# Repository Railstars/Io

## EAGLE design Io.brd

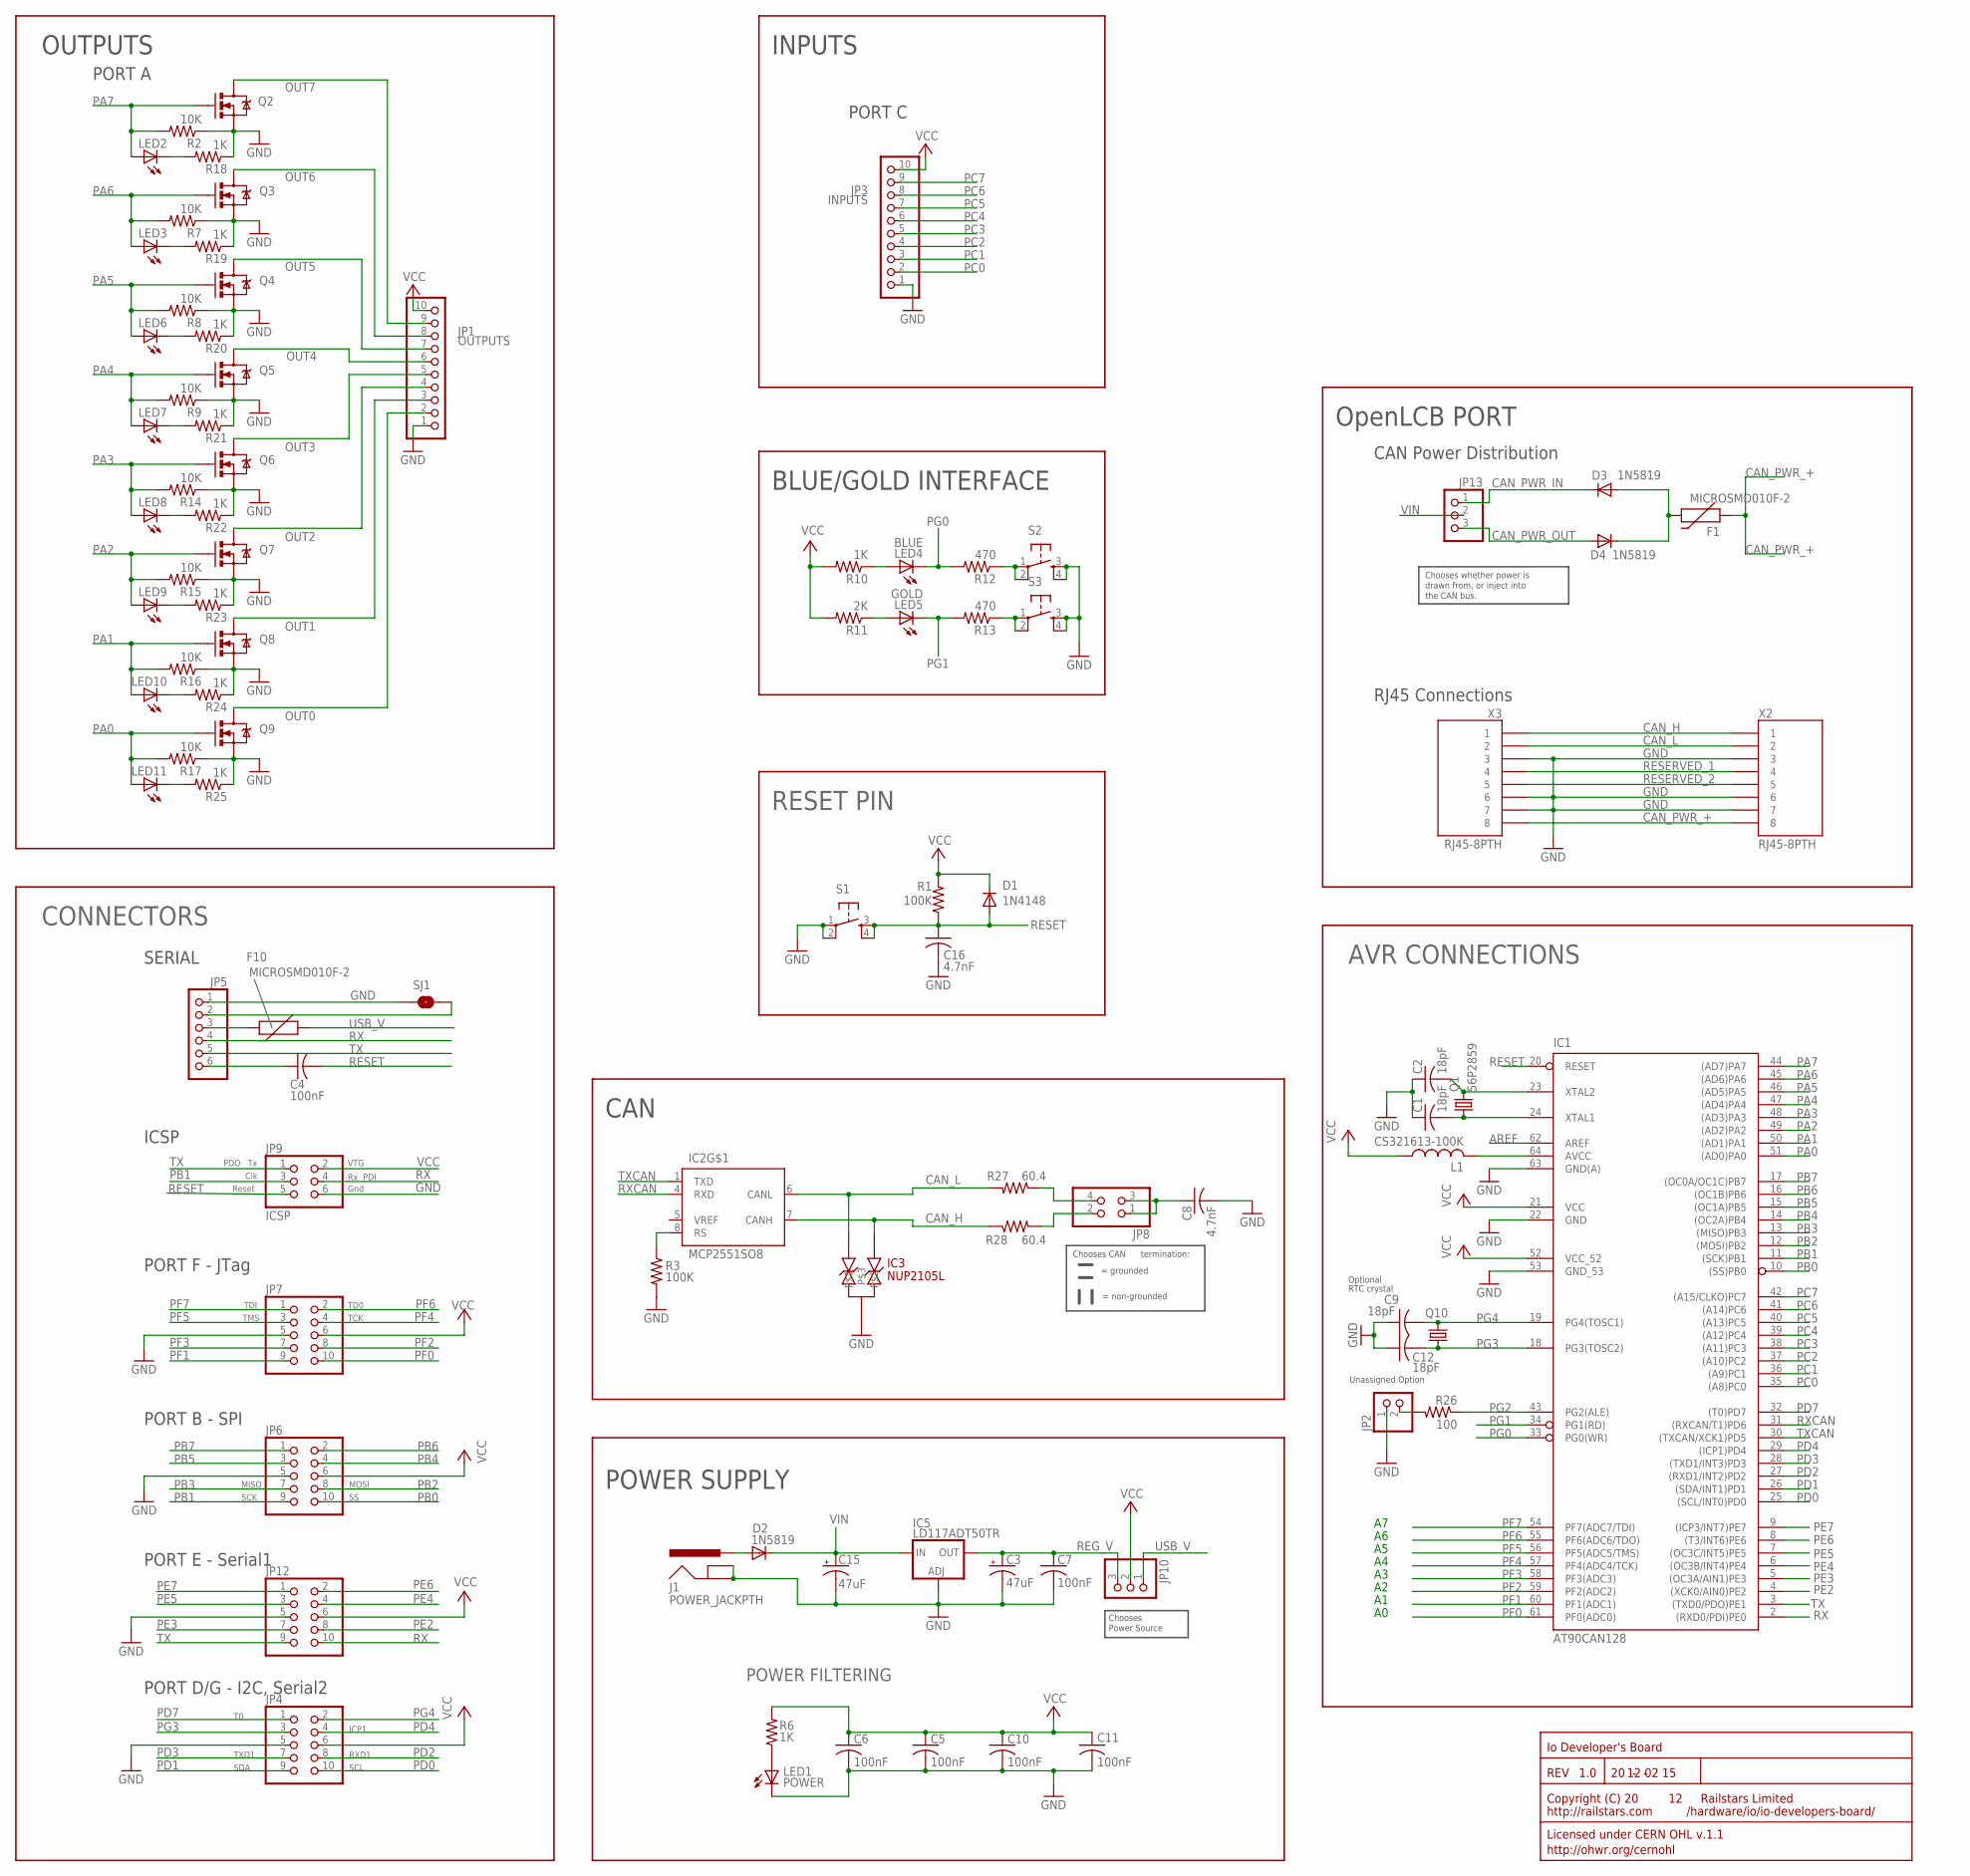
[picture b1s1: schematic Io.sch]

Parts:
C1, C2, C9, C12: 18pF; C0805
C3, C15: 47uF; UD-6,3X5,8_NICHICON
C4, C5, C6, C7, C10, C11: 100nF; C0805
C8, C16: 4.7nF; C0805
D1: 1N4148; SOD123
D2, D3, D4: 1N5819; SMA-DIODE
F1, F10: MICROSMD010F-2; PTC-1206
IC1: AT90CAN128; TQFP64
IC2: MCP2551SO8; SO08
IC3: NUP2105L; SOT-23
IC5: LD117ADT50TR; DPACK
J1: POWER_JACKPTH; POWER_JACK_PTH
JP1: OUTPUTS; 1X10
JP2: PINHD-1X2; 1X02
JP3: INPUTS; 1X10
JP4, JP6, JP7, JP12: 2X5_HEADERSHROUDED; 2X5_SHROUD
JP5: PINHD-1X6; 1X06
JP8: PINHD-2X2; 2X02
JP9: ICSP; 2X03
JP10, JP13: PINHD-1X3; 1X03
L1: CS321613-100K; L3216C
LED1: POWER; CHIP-LED0805
LED2, LED3, LED6, LED7, LED8, LED9, LED10, LED11: LEDCHIP-LED0805; CHIP-LED0805
LED4: BLUE; CHIP-LED0805
LED5: GOLD; CHIP-LED0805
Q1: 56P2859; HC49/S
Q2, Q3, Q4, Q5, Q6, Q7, Q8, Q9: PMV56XN; SOT23-3
Q10: CRYSTALTC26V; TC26V
R1, R3: 100K; R0805
R2, R7, R8, R9, R14, R15, R16, R17: 10K; R0805
R6, R10, R18, R19, R20, R21, R22, R23, R24, R25: 1K; R0805
R11: 2K; R0805
R12, R13: 470; R0805
R26: 100; R0805
R27, R28: 60.4; R1206
S1, S2, S3: TAC_SWITCHPTH; TACTILE-PTH
SJ1: SOLDERJUMPERTRACE; SJ_2S-TRACE
U$4: RAILSTARS_LOGO50MM; RAILSTARS_50MM
X2, X3: RJ45-8PTH; RJ45-8

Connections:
AREF: IC1.62 (AREF)
CAN_H: IC2.7 (CANH), IC3.2, R28.1, X2.1, X3.1
CAN_L: IC2.6 (CANL), IC3.1, R27.2, X2.2, X3.2
CAN_PWR_+: F1.1, X2.8, X3.8
CAN_PWR_IN: D3.C, JP13.1
CAN_PWR_OUT: D4.A, JP13.3
GND: C1.1, C2.1, C3.-, C5.2, C6.2, C7.2, C8.2, C9.1, C10.2, C11.2, C12.1, C15.-, C16.2, IC1.22 (GND), IC1.53 (GND_53), IC1.63 (GND(A)), IC2.2 (GND), IC3.3, IC5.1 (ADJ), J1.GND, J1.GNDBREAK, JP1.1, JP2.1, JP3.1, JP4.5, JP5.1, JP6.5, JP7.5, JP9.6, JP12.5, LED1.C, Q2.2 (S), Q3.2 (S), Q4.2 (S), Q5.2 (S), Q6.2 (S), Q7.2 (S), Q8.2 (S), Q9.2 (S), R2.1, R3.2, R7.1, R8.1, R9.1, R14.1, R15.1, R16.1, R17.1, R18.1, R19.1, R20.1, R21.1, R22.1, R23.1, R24.1, R25.1, S1.1, S1.2, S2.3, S2.4, S3.3, S3.4, SJ1.2, X2.3, X2.6, X2.7, X3.3, X3.6, X3.7
unnamed: JP8.2, R28.2
unnamed: JP8.4, R27.1
unnamed: LED4.A, R10.1
unnamed: LED5.A, R11.1
unnamed: IC2.8 (RS), R3.1
unnamed: R12.1, S2.1, S2.2
unnamed: F10.2, JP5.3
unnamed: LED1.A, R6.1
unnamed: D2.A, J1.PWR
unnamed: C1.2, IC1.24 (XTAL1), Q1.1
unnamed: R13.1, S3.1, S3.2
unnamed: LED10.C, R24.2
unnamed: LED9.C, R23.2
unnamed: LED8.C, R22.2
unnamed: D3.A, D4.C, F1.2
unnamed: LED7.C, R21.2
unnamed: LED6.C, R20.2
unnamed: LED3.C, R19.2
unnamed: LED2.C, R18.2
unnamed: LED11.C, R25.2
unnamed: IC1.64 (AVCC), L1.2
unnamed: JP5.2, SJ1.1
unnamed: C8.1, JP8.1, JP8.3
unnamed: JP2.2, R26.2
unnamed: C4.1, JP5.6
OUT0: JP1.2, Q9.3 (D)
OUT1: JP1.3, Q8.3 (D)
OUT2: JP1.4, Q7.3 (D)
OUT3: JP1.5, Q6.3 (D)
OUT4: JP1.6, Q5.3 (D)
OUT5: JP1.7, Q4.3 (D)
OUT6: JP1.8, Q3.3 (D)
OUT7: JP1.9, Q2.3 (D)
PA0: IC1.51 ((AD0)PA0), LED11.A, Q9.1 (G), R17.2
PA1: IC1.50 ((AD1)PA1), LED10.A, Q8.1 (G), R16.2
PA2: IC1.49 ((AD2)PA2), LED9.A, Q7.1 (G), R15.2
PA3: IC1.48 ((AD3)PA3), LED8.A, Q6.1 (G), R14.2
PA4: IC1.47 ((AD4)PA4), LED7.A, Q5.1 (G), R9.2
PA5: IC1.46 ((AD5)PA5), LED6.A, Q4.1 (G), R8.2
PA6: IC1.45 ((AD6)PA6), LED3.A, Q3.1 (G), R7.2
PA7: IC1.44 ((AD7)PA7), LED2.A, Q2.1 (G), R2.2
PB0: IC1.10 ((SS)PB0), JP6.10
PB1: IC1.11 ((SCK)PB1), JP6.9, JP9.3
PB2: IC1.12 ((MOSI)PB2), JP6.8
PB3: IC1.13 ((MISO)PB3), JP6.7
PB4: IC1.14 ((OC2A)PB4), JP6.4
PB5: IC1.15 ((OC1A)PB5), JP6.3
PB6: IC1.16 ((OC1B)PB6), JP6.2
PB7: IC1.17 ((OC0A/OC1C)PB7), JP6.1
PC0: IC1.35 ((A8)PC0), JP3.2
PC1: IC1.36 ((A9)PC1), JP3.3
PC2: IC1.37 ((A10)PC2), JP3.4
PC3: IC1.38 ((A11)PC3), JP3.5
PC4: IC1.39 ((A12)PC4), JP3.6
PC5: IC1.40 ((A13)PC5), JP3.7
PC6: IC1.41 ((A14)PC6), JP3.8
PC7: IC1.42 ((A15/CLKO)PC7), JP3.9
PD0: IC1.25 ((SCL/INT0)PD0), JP4.10
PD1: IC1.26 ((SDA/INT1)PD1), JP4.9
PD2: IC1.27 ((RXD1/INT2)PD2), JP4.8
PD3: IC1.28 ((TXD1/INT3)PD3), JP4.7
PD4: IC1.29 ((ICP1)PD4), JP4.4
PD7: IC1.32 ((T0)PD7), JP4.1
PE2: IC1.4 ((XCK0/AIN0)PE2), JP12.8
PE3: IC1.5 ((OC3A/AIN1)PE3), JP12.7
PE4: IC1.6 ((OC3B/INT4)PE4), JP12.4
PE5: IC1.7 ((OC3C/INT5)PE5), JP12.3
PE6: IC1.8 ((T3/INT6)PE6), JP12.2
PE7: IC1.9 ((ICP3/INT7)PE7), JP12.1
PF0: IC1.61 (PF0(ADC0)), JP7.10
PF1: IC1.60 (PF1(ADC1)), JP7.9
PF2: IC1.59 (PF2(ADC2)), JP7.8
PF3: IC1.58 (PF3(ADC3)), JP7.7
PF4: IC1.57 (PF4(ADC4/TCK)), JP7.4
PF5: IC1.56 (PF5(ADC5/TMS)), JP7.3
PF6: IC1.55 (PF6(ADC6/TDO)), JP7.2
PF7: IC1.54 (PF7(ADC7/TDI)), JP7.1
PG0: IC1.33 (PG0(WR)), LED4.C, R12.2
PG1: IC1.34 (PG1(RD)), LED5.C, R13.2
PG2: IC1.43 (PG2(ALE)), R26.1
PG3: C12.2, IC1.18 (PG3(TOSC2)), JP4.3, Q10.1
PG4: C9.2, IC1.19 (PG4(TOSC1)), JP4.2, Q10.2
REG_V: C3.+, C7.1, IC5.4 (OUT), JP10.3
RESERVED_1: X2.4, X3.4
RESERVED_2: X2.5, X3.5
RESET: C4.2, C16.1, D1.A, IC1.20 (RESET), JP9.5, R1.1, S1.3, S1.4
RX: IC1.2 ((RXD0/PDI)PE0), JP5.4, JP9.4, JP12.10
RXCAN: IC1.31 ((RXCAN/T1)PD6), IC2.4 (RXD)
TX: IC1.3 ((TXD0/PDO)PE1), JP5.5, JP9.1, JP12.9
TXCAN: IC1.30 ((TXCAN/XCK1)PD5), IC2.1 (TXD)
USB_V: F10.1, JP10.1
VCC: C5.1, C6.1, C10.1, C11.1, D1.C, IC1.21 (VCC), IC1.52 (VCC_52), IC2.3 (VCC), JP1.10, JP3.10, JP4.6, JP6.6, JP7.6, JP9.2, JP10.2, JP12.6, L1.1, R1.2, R6.2, R10.2, R11.2
VIN: C15.+, D2.C, IC5.3 (IN), JP13.2
XTAL1: C2.2, IC1.23 (XTAL2), Q1.2

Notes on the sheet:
POWER SUPPLY
OpenLCB PORT
CAN
POWER FILTERING
RESET PIN
AVR CONNECTIONS
Io Developer's Board
12 02 15
1.0
/hardware/io/io-developers-board/
BLUE/GOLD INTERFACE
Licensed under CERN OHL v.1.1
http://ohwr.org/cernohl
VTG
Clk
Gnd
Reset
TDI
TD0
TMS
TCK
SCL
SDA
RXD1
TXD1
ICP1
SCK
MOSI
MISO
PDO
PDI
INPUTS
OUTPUTS
CONNECTORS
PORT F - JTag
PORT B - SPI
PORT E - Serial1
PORT D/G - I2C, Serial2
PORT A
PORT C

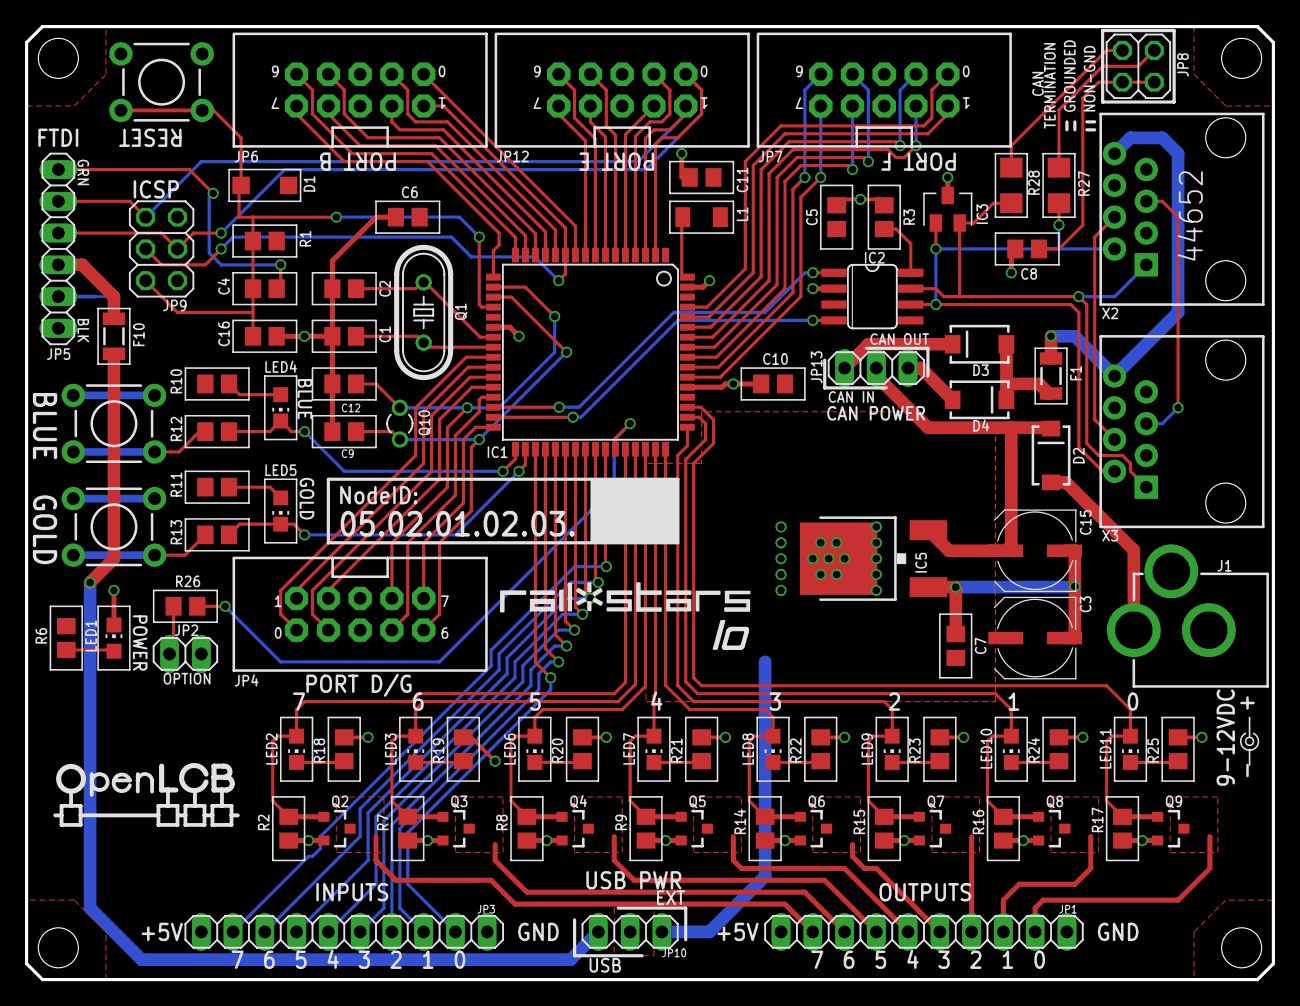
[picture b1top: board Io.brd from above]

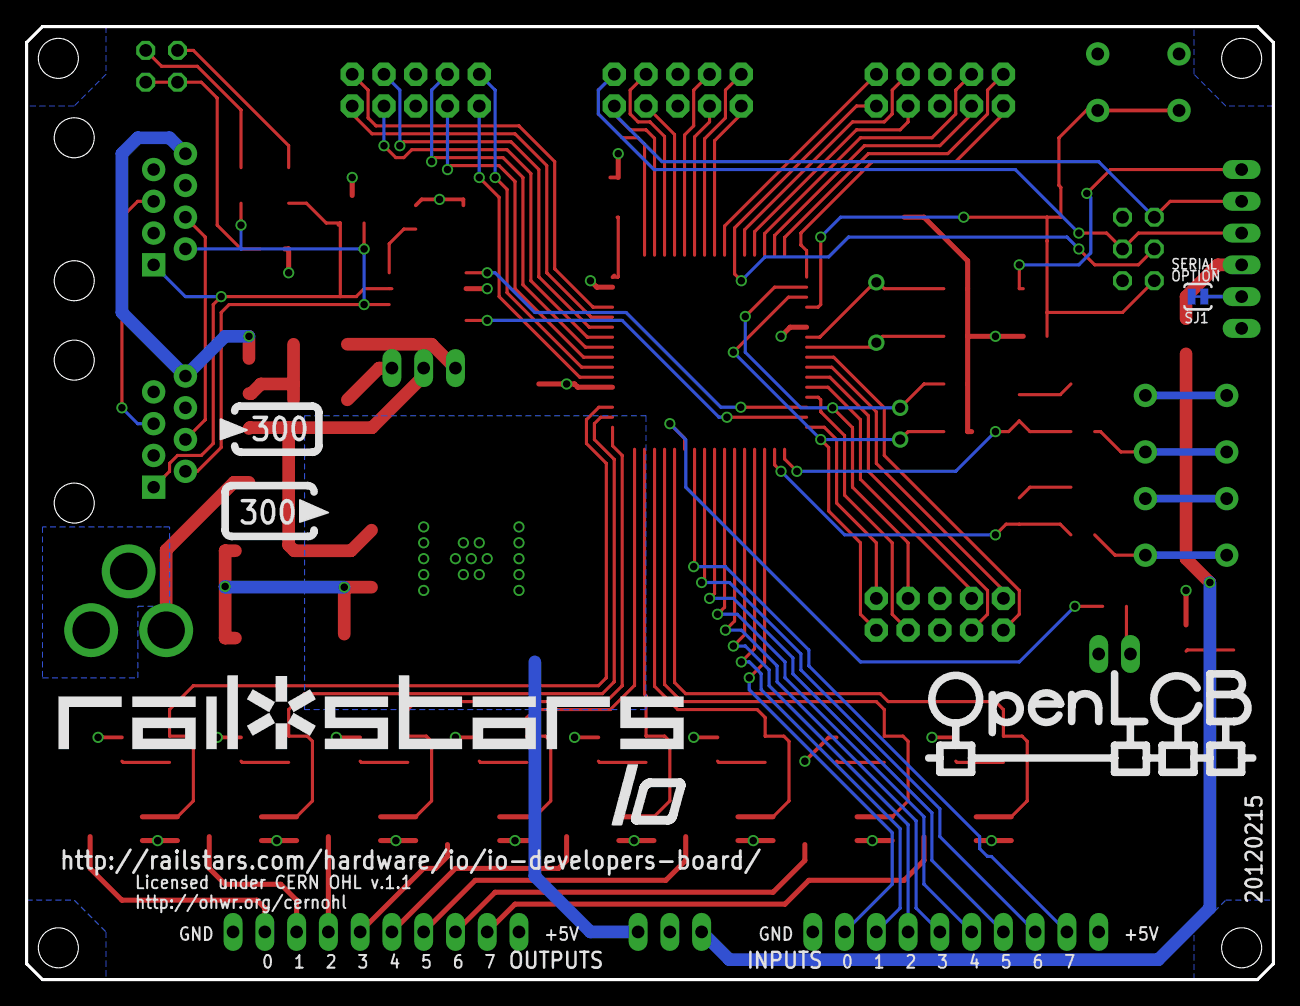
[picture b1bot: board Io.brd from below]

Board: 2 copper layers, 99.7 x 76.2 mm, 99 parts (3 on the bottom side), 100 nets.

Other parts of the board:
U$1: RAILSTARS_LOGO_IO_V
U$3: RAILSTARS_1IN
U$7: RAILSTARS_LOGO_IO_LARGE_V_INV
U$8: CURRENT_DRAWV_INV
U$9: OPENLCB_LOGOV
U$11: CURRENT_PROVIDEV_INV
U$13: OPENLCB_OPENLCB_LOGO_LARGE

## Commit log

2011-12-01 IO_Board
2011-12-04 daughter
2011-12-05 daughter REV B
2011-12-06 daughter REV C
2011-12-07 daughter_output
2011-12-10 daughter REV D-BACKUP
2011-12-10 IO 20111210
2011-12-11 IO 20111211
2011-12-11 IO 20111212
2011-12-12 IO 20111213
2011-12-13 IO 20111214
2011-12-14 IO 20111215
2012-01-30 Io 20120103
2012-02-15 Io 20120215
2013-08-08 Io retail firmware 1.0

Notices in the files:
Io.brd:
Copyright (C) 2012 D.E. Goodman-Wilson
parts and their libraries:
Artificial Science: Copyright (C) 20
